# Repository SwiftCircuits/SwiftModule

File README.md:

# SwiftModule
A repo containing production files for a large variety of modules of sensors or other integrated circuits.

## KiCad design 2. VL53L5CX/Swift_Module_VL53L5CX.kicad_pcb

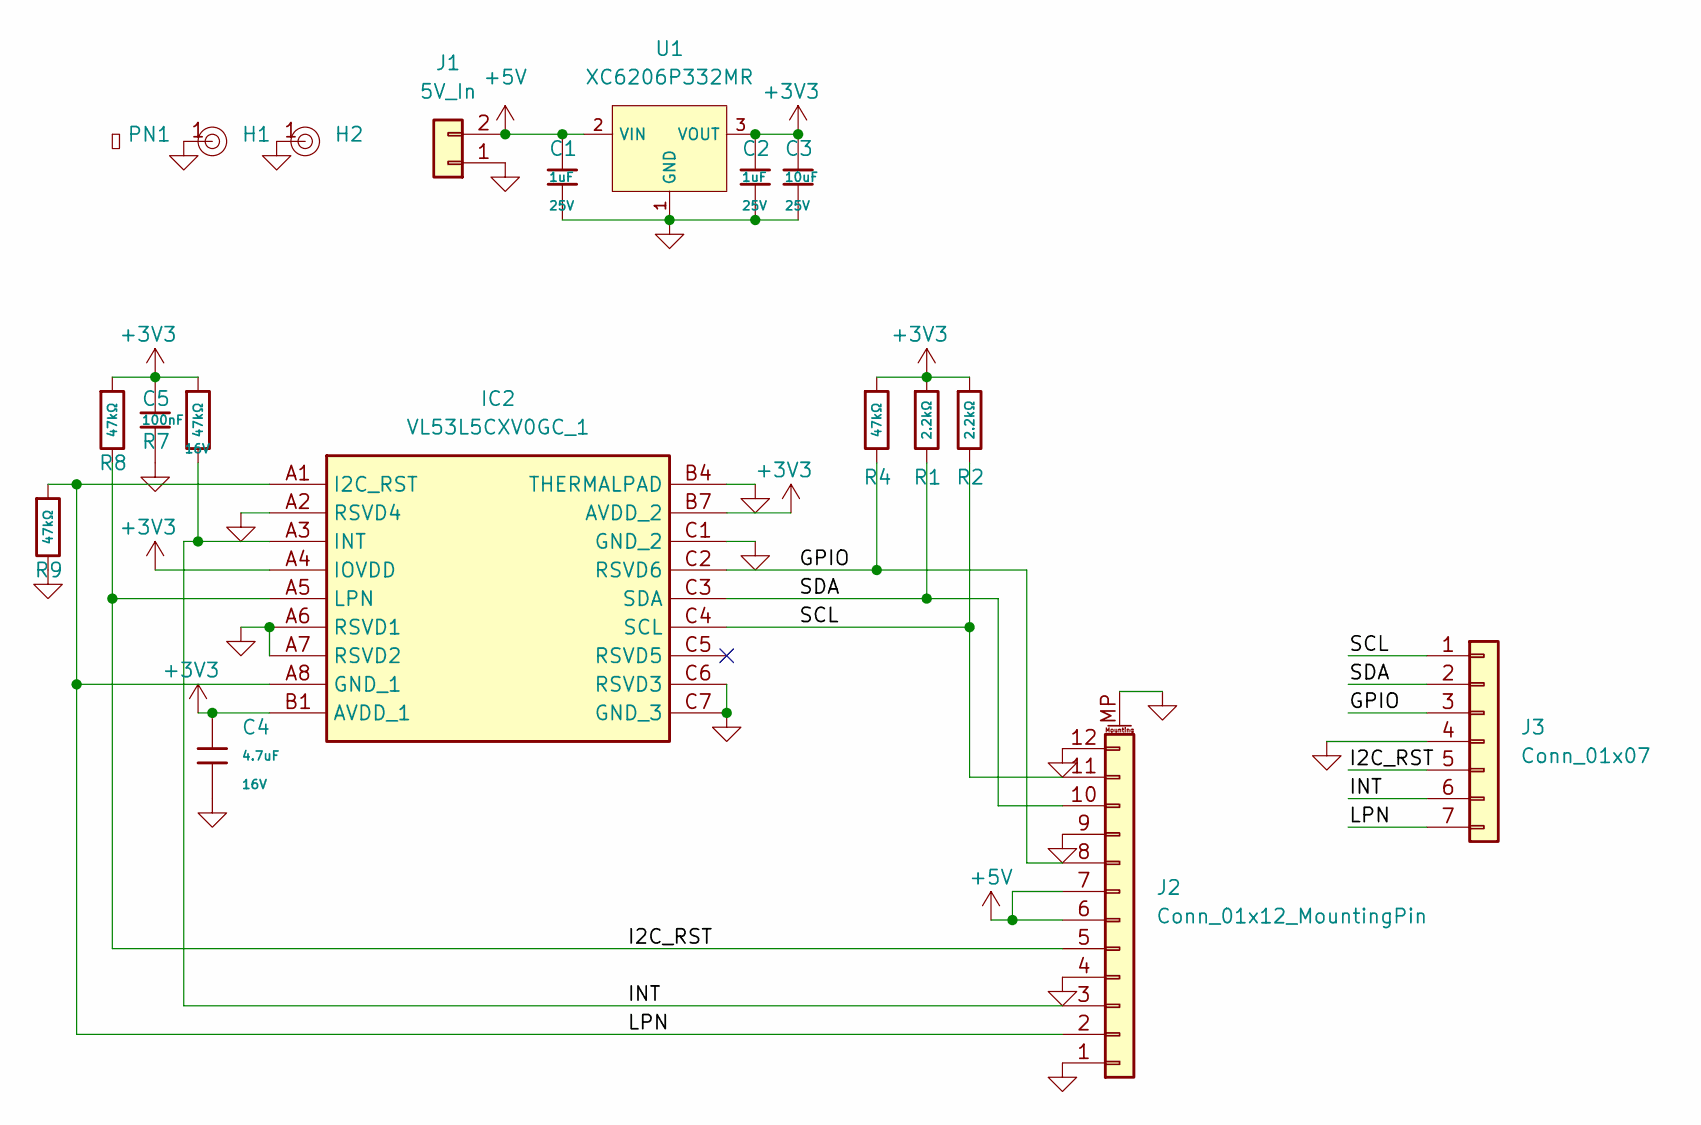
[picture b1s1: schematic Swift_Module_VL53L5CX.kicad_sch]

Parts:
C1, C2: 1uF; C_0402; Voltage Rated 25V; Tolerance ±10%; Part CL05A105KA5NQNC; LCSC C52923
C3: 10uF; C_0603; Voltage Rated 25V; Tolerance ±20%; Part CL10A106MA8NRNC; LCSC C96446
C4: 4.7uF; C_0603; Voltage Rated 16V; Tolerance ±10%; Part CL10A475KO8NNNC; LCSC C19666
C5: 100nF; C_0402; Voltage Rated 16V; Tolerance ±10%; Part CL05B104KO5NNNC; LCSC C1525
H1, H2: Hole, 3mm
IC2: VL53L5CXV0GC_1; VL53L5CXV0GC1; Mouser Part Number 511-VL53L5CXV0GC/1
J1: 5V_In; JST_XH_B2B-XH-A_1x02_P2.50mm_Vertical
J2: Conn_01x12_MountingPin; Hirose_FH12-12S-0.5SH_1x12-1MP_P0.50mm_Horizontal; LCSC C88360
J3: Conn_01x07; PinHeader_1x07_P2.54mm_Vertical
PN1: Part_Num_JLCPCB
R1, R2: 2.2kΩ; R_0402; Overload Voltage (Max) 50V; Tolerance ±1%; Part 0402WGF2201TCE; LCSC C25879
R4, R7, R8, R9: 47kΩ; R_0402; Overload Voltage (Max) 50V; Tolerance ±1%; Part 0402WGF4702TCE; LCSC C25792
U1: XC6206P332MR; SOT-23-3_L2.9-W1.6-P1.90-LS2.8-BR; Output Voltage 3.3V; Dropout Voltage 680mV@(100mA); Part XC6206P332MR-G; LCSC C5446

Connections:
+3V3: C2.1, C3.1, C4.1, C5.1, IC2.A4 (IOVDD), IC2.B1 (AVDD_1), IC2.B7 (AVDD_2), R1.1, R2.1, R4.1, R7.1, R8.1, U1.3 (VOUT)
+5V: C1.1, J1.2, J2.6, J2.7, U1.2 (VIN)
/GPIO: IC2.C2 (RSVD6), J2.8, J3.3, R4.2
/I2C_RST: IC2.A5 (LPN), J2.5, J3.5, R8.2
/INT: IC2.A3 (INT), J2.3, J3.6, R7.2
/LPN: IC2.A1 (I2C_RST), IC2.A8 (GND_1), J2.2, J3.7, R9.1
/SCL: IC2.C4 (SCL), J2.11, J3.1, R2.2
/SDA: IC2.C3 (SDA), J2.10, J3.2, R1.2
GND: C1.2, C2.2, C3.2, C4.2, C5.2, H1.1, H2.1, IC2.A2 (RSVD4), IC2.A6 (RSVD1), IC2.A7 (RSVD2), IC2.B4 (THERMALPAD), IC2.C1 (GND_2), IC2.C6 (RSVD3), IC2.C7 (GND_3), J1.1, J2.1, J2.4, J2.9, J2.12, J2.MP (MountPin), J3.4, R9.2, U1.1 (GND)

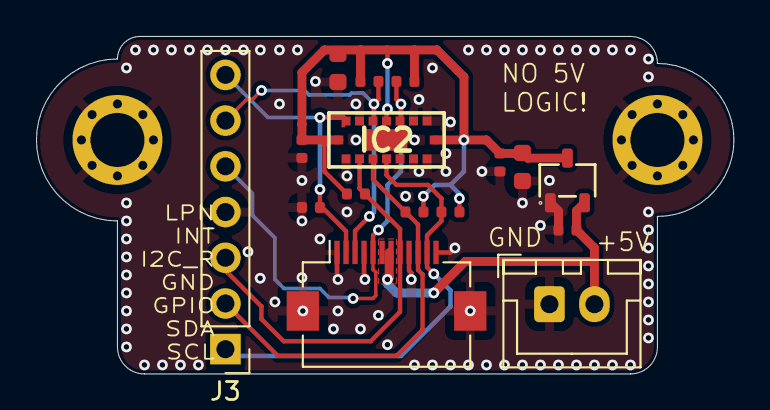
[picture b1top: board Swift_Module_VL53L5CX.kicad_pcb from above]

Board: 4 copper layers, 38.8 x 18.8 mm, 18 parts (0 on the bottom side), 9 nets.

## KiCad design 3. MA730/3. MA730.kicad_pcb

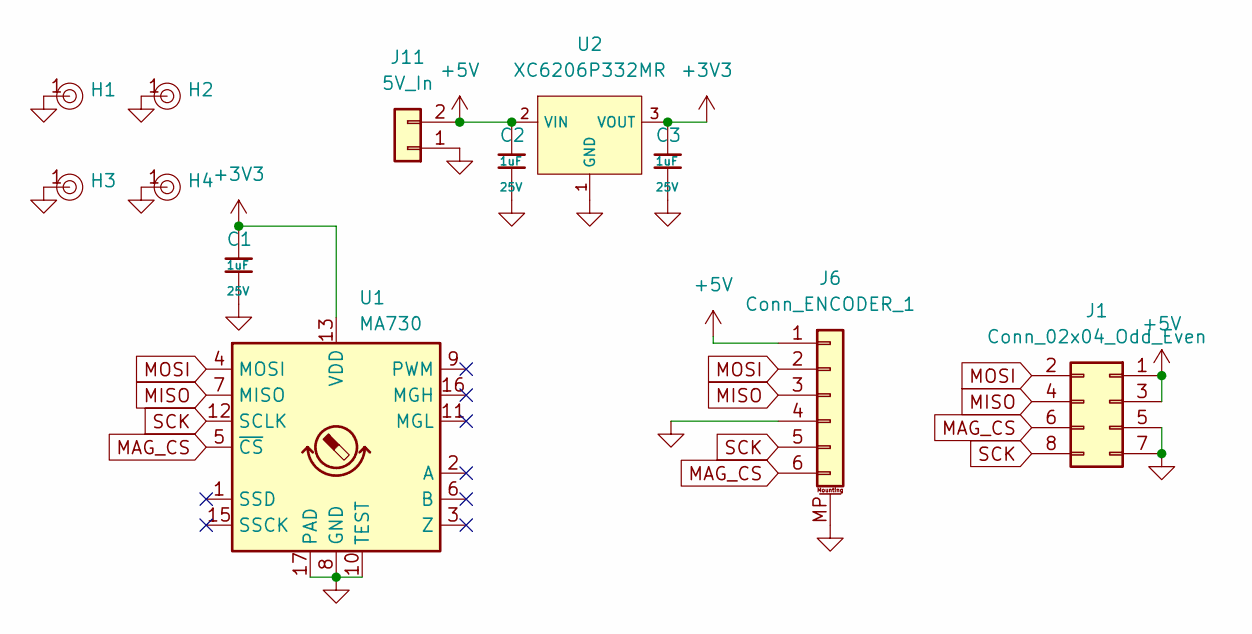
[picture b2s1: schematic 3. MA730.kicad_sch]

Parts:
C1, C2, C3: 1uF; C_0402; Voltage Rated 25V; Tolerance ±10%; Part CL05A105KA5NQNC; LCSC C52923
H1, H2, H3, H4: Hole, 3mm
J1: Conn_02x04_Odd_Even; PinHeader_2x04_P2.54mm_Vertical
J6: Conn_ENCODER_1; Hirose_FH12-6S-0.5SH_1x06-1MP_P0.50mm_Horizontal
J11: 5V_In; JST_XH_B2B-XH-A_1x02_P2.50mm_Vertical
U1: MA730; QFN-16-1EP_3x3mm_P0.5mm_EP1.75x1.75mm
U2: XC6206P332MR; SOT-23-3_L2.9-W1.6-P1.90-LS2.8-BR; Output Voltage 3.3V; Dropout Voltage 680mV@(100mA); Part XC6206P332MR-G; LCSC C5446

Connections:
+3V3: C1.1, C3.1, U1.13 (VDD), U2.3 (VOUT)
+5V: C2.1, J1.1, J1.3, J6.1, J11.2, U2.2 (VIN)
GND: C1.2, C2.2, C3.2, H1.1, H2.1, H3.1, H4.1, J1.5, J1.7, J6.4, J6.MP (MountPin), J11.1, U1.8 (GND), U1.10 (TEST), U1.17 (PAD), U2.1 (GND)
MAG_CS: J1.6, J6.6, U1.5 (~CS)
MISO: J1.4, J6.3, U1.7 (MISO)
MOSI: J1.2, J6.2, U1.4 (MOSI)
SCK: J1.8, J6.5, U1.12 (SCLK)

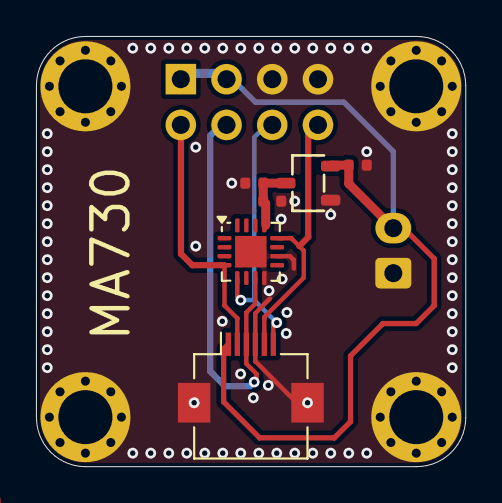
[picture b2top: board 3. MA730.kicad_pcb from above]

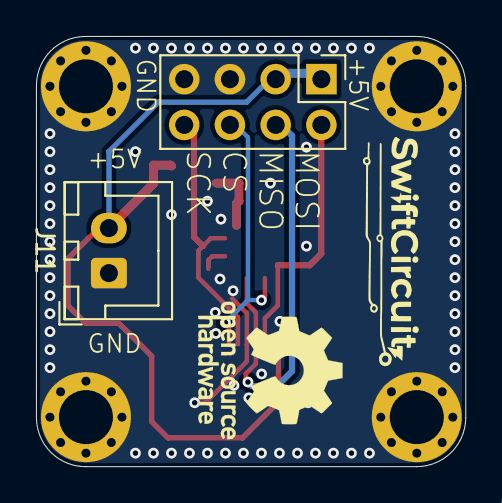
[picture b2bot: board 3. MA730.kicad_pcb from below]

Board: 4 copper layers, 23.8 x 23.9 mm, 12 parts (2 on the bottom side), 7 nets.

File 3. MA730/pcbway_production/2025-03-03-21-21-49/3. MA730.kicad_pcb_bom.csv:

Designator,Quantity,Value,Footprint,Package,MPN,DNP,Mount_Type,Description,LCSC,Stock,Price,Process,Minimum Qty,Attrition Qty,Class,Category,Manufacturer,Part,Voltage Rated,Tolerance,Capacitance,Temperature Coefficient,Number Of Outputs,Output Voltage,Dropout Voltage,Output Current,Output Type,Maximum Input Voltage,Output Polarity,Feature
"C1, C2, C3",3,1uF,C_0402,,,,smt,25V 1uF X5R ±10% 0402 Multilayer Ceramic Capacitors MLCC - SMD/SMT ROHS,C52923,7796525,0.006USD,SMT,20,10,Basic Component,"Capacitors,Multilayer Ceramic Capacitors MLCC - SMD/SMT",Samsung Electro-Mechanics,CL05A105KA5NQNC,25V,±10%,1uF,X5R,,,,,,,,
"H1, H2, H3, H4",4,~,"Hole, 3mm",,,,tht,,,,,,,,,,,,,,,,,,,,,,,
J1,1,Conn_02x04_Odd_Even,PinHeader_2x04_P2.54mm_Vertical,,,,tht,"Generic connector, double row, 02x04, odd/even pin numbering scheme (row 1 odd numbers, row 2 even numbers), script generated (kicad-library-utils/schlib/autogen/connector/)",,,,,,,,,,,,,,,,,,,,,,
J11,1,5V_In,JST_XH_B2B-XH-A_1x02_P2.50mm_Vertical,,,,tht,"Generic connector, single row, 01x02, script generated (kicad-library-utils/schlib/autogen/connector/)",,,,,,,,,,,,,,,,,,,,,,
J6,1,Conn_ENCODER_1,Hirose_FH12-6S-0.5SH_1x06-1MP_P0.50mm_Horizontal,,,,smt,"Generic connectable mounting pin connector, single row, 01x06, script generated (kicad-library-utils/schlib/autogen/connector/)",,,,,,,,,,,,,,,,,,,,,,
U1,1,MA730,QFN-16-1EP_3x3mm_P0.5mm_EP1.75x1.75mm,,,,smt,"Magnetic rotary angle sensor, 14-bit, SPI interface, ABZ, PWM, QFN-16",,,,,,,,,,,,,,,,,,,,,,
U2,1,XC6206P332MR,SOT-23-3_L2.9-W1.6-P1.90-LS2.8-BR,,,,smt,"200mA Fixed 3.3V Positive electrode 6V SOT-23-3L Voltage Regulators - Linear, Low Drop Out (LDO) Regulators ROHS",C5446,403960,0.093USD,SMT,5,2,Basic Component,"Power Management ICs,Linear Voltage Regulators (LDO)",Torex Semicon,XC6206P332MR-G,,,,,1,3.3V,680mV@(100mA),200mA,Fixed,6V,Positive electrode,Low ESR;Overcurrent Protection(OCP)

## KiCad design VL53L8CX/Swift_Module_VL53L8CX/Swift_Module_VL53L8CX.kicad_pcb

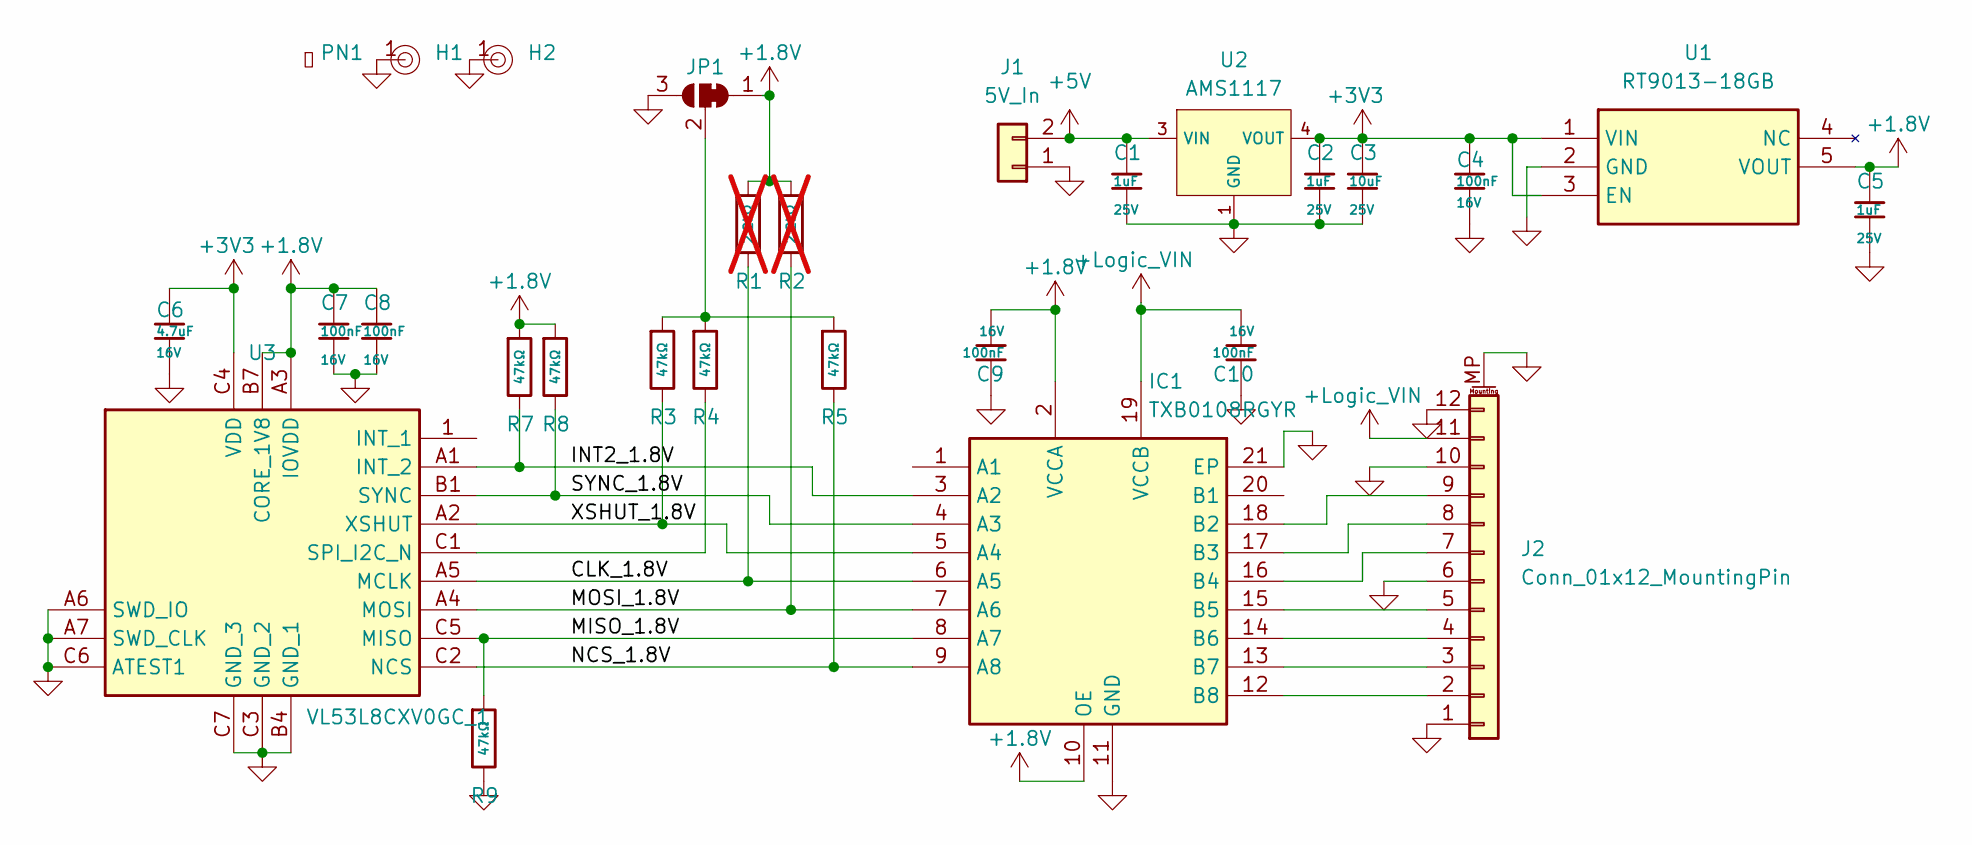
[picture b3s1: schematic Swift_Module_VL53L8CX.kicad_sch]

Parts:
C1, C2, C5: 1uF; C_0402; Voltage Rated 25V; Tolerance ±10%; Part CL05A105KA5NQNC; LCSC C52923
C3: 10uF; C_0603; Voltage Rated 25V; Tolerance ±20%; Part CL10A106MA8NRNC; LCSC C96446
C4, C7, C8, C9, C10: 100nF; C_0402; Voltage Rated 16V; Tolerance ±10%; Part CL05B104KO5NNNC; LCSC C1525
C6: 4.7uF; C_0603; Voltage Rated 16V; Tolerance ±10%; Part CL10A475KO8NNNC; LCSC C19666
H1, H2: Hole, 3mm
IC1: TXB0108RGYR; SN74LVC541ARGYR; Mouser Part Number 595-TXB0108RGYR
J1: 5V_In; JST_XH_B2B-XH-A_1x02_P2.50mm_Vertical
J2: Conn_01x12_MountingPin; Hirose_FH12-12S-0.5SH_1x12-1MP_P0.50mm_Horizontal; LCSC C88360
JP1: SolderJumper_3_Bridged12; SolderJumper-3_P1.3mm_Bridged2Bar12_RoundedPad1.0x1.5mm
PN1: Part_Num_JLCPCB
R1, R2: 2.2kΩ; R_0402; Overload Voltage (Max) 50V; Tolerance ±1%; Part 0402WGF2201TCE; LCSC C25879; not fitted
R3, R4, R5, R7, R8, R9: 47kΩ; R_0402; Overload Voltage (Max) 50V; Tolerance ±1%; Part 0402WGF4702TCE; LCSC C25792
U1: RT9013-18GB; SOT94P279X130-5N; Mouser Part Number 835-RT9013-18GB
U2: AMS1117; SOT-223-3_L6.5-W3.4-P2.30-LS7.0-BR; Output Voltage 3.3V; Dropout Voltage 1.3V@(800mA); Part AMS1117-3.3; LCSC C6186
U3: VL53L8CXV0GC_1; VL53L8CXV0GC1; Mouser Part Number 511-VL53L8CXV0GC/1

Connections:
+1.8V: C5.1, C7.1, C8.1, C9.2, IC1.2 (VCCA), IC1.10 (OE), JP1.1 (A), R1.1, R2.1, R7.1, R8.1, U1.5 (VOUT), U3.A3 (IOVDD), U3.B7 (CORE_1V8)
+3V3: C2.1, C3.1, C4.1, C6.1, U1.1 (VIN), U1.3 (EN), U2.2 (VOUT), U2.4 (VOUT), U3.C4 (VDD)
+5V: C1.1, J1.2, U2.3 (VIN)
+Logic_VIN: C10.2, IC1.19 (VCCB), J2.11
/CLK_1.8V: IC1.6 (A5), R1.2, U3.A5 (MCLK)
/INT2_1.8V: IC1.3 (A2), R7.2, U3.A1 (INT_2)
/MISO_1.8V: IC1.8 (A7), R9.1, U3.C5 (MISO)
/MOSI_1.8V: IC1.7 (A6), R2.2, U3.A4 (MOSI)
/NCS_1.8V: IC1.9 (A8), R5.2, U3.C2 (NCS)
/SYNC_1.8V: IC1.4 (A3), R8.2, U3.B1 (SYNC)
/XSHUT_1.8V: IC1.5 (A4), R3.2, U3.A2 (XSHUT)
GND: C1.2, C2.2, C3.2, C4.2, C5.2, C6.2, C7.2, C8.2, C9.1, C10.1, H1.1, H2.1, IC1.11 (GND), IC1.21 (EP), J1.1, J2.1, J2.6, J2.10, J2.12, J2.MP (MountPin), JP1.3 (B), R9.2, U1.2 (GND), U2.1 (GND), U3.A6 (SWD_IO), U3.A7 (SWD_CLK), U3.B4 (GND_1), U3.C3 (GND_2), U3.C6 (ATEST1), U3.C7 (GND_3)
unnamed: IC1.18 (B2), J2.9
unnamed: IC1.17 (B3), J2.8
unnamed: IC1.16 (B4), J2.7
unnamed: IC1.15 (B5), J2.5
unnamed: IC1.14 (B6), J2.4
unnamed: IC1.13 (B7), J2.3
unnamed: IC1.12 (B8), J2.2
unnamed: JP1.2 (C), R3.1, R4.1, R5.1
unnamed: R4.2, U3.C1 (SPI_I2C_N)

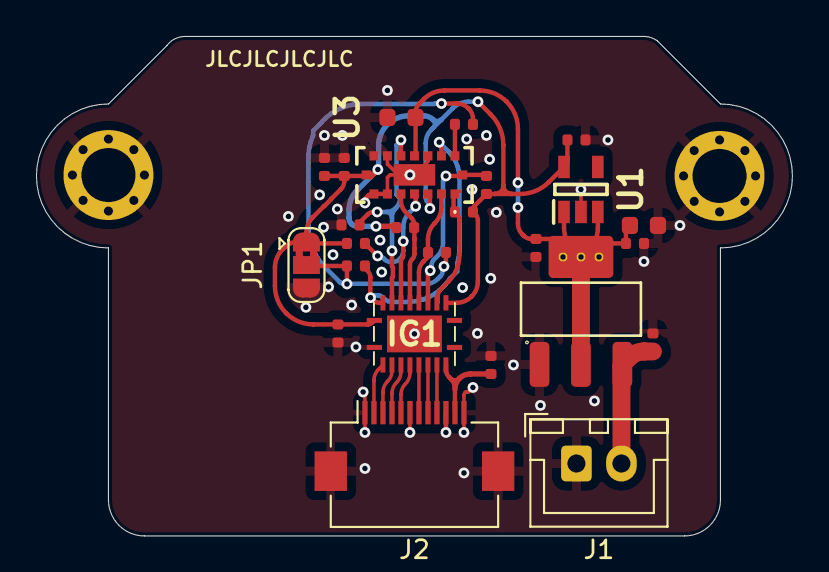
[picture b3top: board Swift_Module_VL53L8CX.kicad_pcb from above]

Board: 4 copper layers, 42.0 x 27.8 mm, 28 parts (0 on the bottom side), 21 nets.

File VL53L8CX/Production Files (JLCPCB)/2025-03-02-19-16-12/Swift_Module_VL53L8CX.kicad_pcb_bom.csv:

Designator,Quantity,Value,Footprint,Package,MPN,DNP,Mount_Type,Description,LCSC,Stock,Price,Process,Minimum Qty,Attrition Qty,Class,Category,Manufacturer,Part,Voltage Rated,Tolerance,Capacitance,Temperature Coefficient,Height,Mouser Part Number,Mouser Price/Stock,Manufacturer_Name,Resistance,Power(Watts),Type,Overload Voltage (Max),Operating Temperature Range,JCSC,Number Of Outputs,Output Voltage,Dropout Voltage,Output Current,Output Type,Output Polarity,Power Supply Rejection Ratio (Psrr),Feature
"C1, C2, C5",3,1uF,C_0402,,,,smt,25V 1uF X5R ±10% 0402 Multilayer Ceramic Capacitors MLCC - SMD/SMT ROHS,C52923,7796525,0.006USD,SMT,20,10,Basic Component,"Capacitors,Multilayer Ceramic Capacitors MLCC - SMD/SMT",Samsung Electro-Mechanics,CL05A105KA5NQNC,25V,±10%,1uF,X5R,,,,,,,,,,,,,,,,,,
"C10, C4, C7, C8, C9",5,100nF,C_0402,,,,smt,16V 100nF X7R ±10% 0402 Multilayer Ceramic Capacitors MLCC - SMD/SMT ROHS,C1525,13104064,0.004USD,SMT,20,10,Basic Component,"Capacitors,Multilayer Ceramic Capacitors MLCC - SMD/SMT",Samsung Electro-Mechanics,CL05B104KO5NNNC,16V,±10%,100nF,X7R,,,,,,,,,,,,,,,,,,
C3,1,10uF,C_0603,,,,smt,25V 10uF X5R ±20% 0603 Multilayer Ceramic Capacitors MLCC - SMD/SMT ROHS,C96446,4331263,0.017USD,SMT,20,8,Basic Component,"Capacitors,Multilayer Ceramic Capacitors MLCC - SMD/SMT",Samsung Electro-Mechanics,CL10A106MA8NRNC,25V,±20%,10uF,X5R,,,,,,,,,,,,,,,,,,
C6,1,4.7uF,C_0603,,,,smt,16V 4.7uF X5R ±10% 0603 Multilayer Ceramic Capacitors MLCC - SMD/SMT ROHS,C19666,2453279,0.013USD,SMT,20,10,Basic Component,"Capacitors,Multilayer Ceramic Capacitors MLCC - SMD/SMT",Samsung Electro-Mechanics,CL10A475KO8NNNC,16V,±10%,4.7uF,X5R,,,,,,,,,,,,,,,,,,
"H1, H2",2,~,"Hole, 3mm",,,,tht,,,,,,,,,,,,,,,,,,,,,,,,,,,,,,,,,
IC1,1,TXB0108RGYR,SN74LVC541ARGYR,,TXB0108RGYR,,smt,8-Bit Bidirectional Voltage-Level Shifter with Auto Direction Sensing and +/-15-kV ESD Protect,C194701,,,,,,,,,,,,,,1,595-TXB0108RGYR,https://www.mouser.co.uk/ProductDetail/Texas-Instruments/TXB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,Texas Instruments,,,,,,,,,,,,,,
J1,1,5V_In,JST_XH_B2B-XH-A_1x02_P2.50mm_Vertical,,,,tht,"Generic connector, single row, 01x02, script generated (kicad-library-utils/schlib/autogen/connector/)",,,,,,,,,,,,,,,,,,,,,,,,,,,,,,,,
J2,1,Conn_01x12_MountingPin,Hirose_FH12-12S-0.5SH_1x12-1MP_P0.50mm_Horizontal,,,,smt,"Generic connectable mounting pin connector, single row, 01x12, script generated (kicad-library-utils/schlib/autogen/connector/)",C88360,,,,,,,,,,,,,,,,,,,,,,,,,,,,,,,
PN1,1,~,Part_Num_JLCPCB,,,,tht,"To indicate the location, simply add the text ""JLCJLCJLCJLC"" to the silk layer and select the ""Specify a location"" option when placing your order. Please note that if this option is not chosen, we may not notice that you have added the text.   Note: Use only ""JLCJLCJLCJLC"" without any additional characters. The font size should be larger than 0.8mm in height and 0.15mm in width.",,,,,,,,,,,,,,,,,,,,,,,,,,,,,,,,
R1,1,2.2kΩ,R_0402,,,Yes,tht,62.5mW Thick Film Resistors 50V ±100ppm/°C ±1% 2.2kΩ 0402 Chip Resistor - Surface Mount ROHS,C25879,903036,0.004USD,SMT,20,10,Basic Component,"Resistors,Chip Resistor - Surface Mount",UNI-ROYAL(Uniroyal Elec),0402WGF2201TCE,,±1%,,±100ppm/°C,,,,,2.2kΩ,62.5mW,Thick Film Resistors,50V,-55°C~+155°C,,,,,,,,,
R2,1,2.2kΩ,R_0402,,,Yes,tht,62.5mW Thick Film Resistors 50V ±100ppm/°C ±1% 2.2kΩ 0402 Chip Resistor - Surface Mount ROHS,C25879,903036,0.004USD,SMT,20,10,Basic Component,"Resistors,Chip Resistor - Surface Mount",UNI-ROYAL(Uniroyal Elec),0402WGF2201TCE,,±1%,,±100ppm/°C,,,,,2.2kΩ,62.5mW,Thick Film Resistors,50V,-55°C~+155°C,,,,,,,,,
"R3, R4, R5, R7, R8, R9",6,47kΩ,R_0402,,,,tht,62.5mW Thick Film Resistors 50V ±100ppm/°C ±1% 47kΩ 0402 Chip Resistor - Surface Mount ROHS,C25792,1796042,0.004USD,SMT,20,10,Basic Component,"Resistors,Chip Resistor - Surface Mount",UNI-ROYAL(Uniroyal Elec),0402WGF4702TCE,,±1%,,±100ppm/°C,,,,,47kΩ,62.5mW,Thick Film Resistors,50V,-55°C~+155°C,,,,,,,,,
U1,1,RT9013-18GB,SOT94P279X130-5N,,RT9013-18GB,,smt,"IC, LDO, FIXED, 1.8V, 0.5A, SOT-23-5; Output Type:Fixed; Input Voltage Min:2.2V; Input Voltage Max:5.5V; Fixed Output Voltage Nom.:1.8V; Adjustable Output Voltage Min:-; Adjustable Output Voltage Max:-; Output Current:500mA; Dropout RoHS Compliant: Yes",,,,,,,,,,,,,,,1.295,835-RT9013-18GB,https://www.mouser.co.uk/ProductDetail/Richtek/RT9013-18GB?q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,RICHTEK,,,,,,C22435116,,,,,,,,
U2,1,AMS1117,SOT-223-3_L6.5-W3.4-P2.30-LS7.0-BR,,,,tht,"72dB@(120Hz) 1A Fixed 3.3V Positive electrode SOT-223 Voltage Regulators - Linear, Low Drop Out (LDO) Regulators ROHS",C6186,1054260,0.148USD,SMT,2,0,Basic Component,"Power Management ICs,Linear Voltage Regulators (LDO)",Advanced Monolithic Systems,AMS1117-3.3,,,,,,,,,,,,,,,1,3.3V,1.3V@(800mA),1A,Fixed,Positive electrode,72dB@(120Hz),Overcurrent Protection(OCP);Thermal Protection(TSD)
U3,1,VL53L8CXV0GC_1,VL53L8CXV0GC1,,VL53L8CXV0GC/1,,smt,"Low-power high-performance 8x8 multizone Time-of-Flight sensor 940 nm, 6.4x3.0x1.75 mm, -30 to 85C",C7386355,,,,,,,,,,,,,,1.8,511-VL53L8CXV0GC/1,https://www.mouser.co.uk/ProductDetail/STMicroelectronics/VL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,STMicroelectronics,,,,,,,,,,,,,,

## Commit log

2025-05-03 I forgor
